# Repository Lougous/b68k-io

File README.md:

# b68k-io
IO extension board for b68k computer.

## Features
- local bus peripheral to [b68k-cpu](https://github.com/Lougous/b68k-cpu) computer
- a UART with DB9 connector (RS232, no hardware flow control)
- an I2C bus with onboard RTC chip (DS1307+) with crystal and backup battery, and 4-pins pin header extension connector
- a SPI bus with 7 chip select lines: 2x SD cards slots, 1x through an 8-pins pin header extension connector, 4x through DB15 connector for external equipements (external SPI slaves are electrically isolated from internal slaves)

Board fonctions are implemented with a PIC18F27K42 microcontroller.

The board has only two memory locations accessible through the expansion bus: one to set the actual register to access, the other to read or write data from/to the register.

| register | address | description             |
|:--------:|:-------:|:------------------------|
| DATA     | XX0000h | register data |
| ADDRESS  | XX0001h | register index |

## Register set

| register    | index   | description             |
|:-----------:|:-------:|:------------------------|
| SPI_SEL     | 0       | [5..3] : enabled SPI chip select line<br>0: external #0<br>1: external #1<br>2: external #2<br>3: external #3<br>4: SD card A<br>5: SD card B<br>6: internal pin header<br>7: none (reset) |
| SPI_CTRL    | 1       | bit 7: BUSY   r<br>bit 2: CLRBF  s<br>bit 1: TXR    rw<br>bit 0: RXR    rw |
| SPI_DATA    | 2       | SPI data in/out |
| UART_STS    | 4       | UART status<br>bit 7: TX ready<br>bit 1: RX FIFO overflow<br>bit 0: RX FIFO underflow |
| UART_DATA   | 5       | UART data in/out |
| I2C_CTRL    | 6       | bit 7: RXIF<br>bit 5: TXBE<br>bit 2: reset<br>bit 1: start<br>bit 0: RXBF |
| I2C_CNT     | 7       | |
| I2C_DATA    | 8       | |
| I2C_CMD     | 9       | bit 7..1: address<br>bit 0:    RWn |
| IRQCFG      | 14      | interrupt controller configuration<br>bit 0: enable UART RX interrupt |
| IRQSTS      | 15      | interrupt controller status<br>bit 0: UART RX interrupt pending |

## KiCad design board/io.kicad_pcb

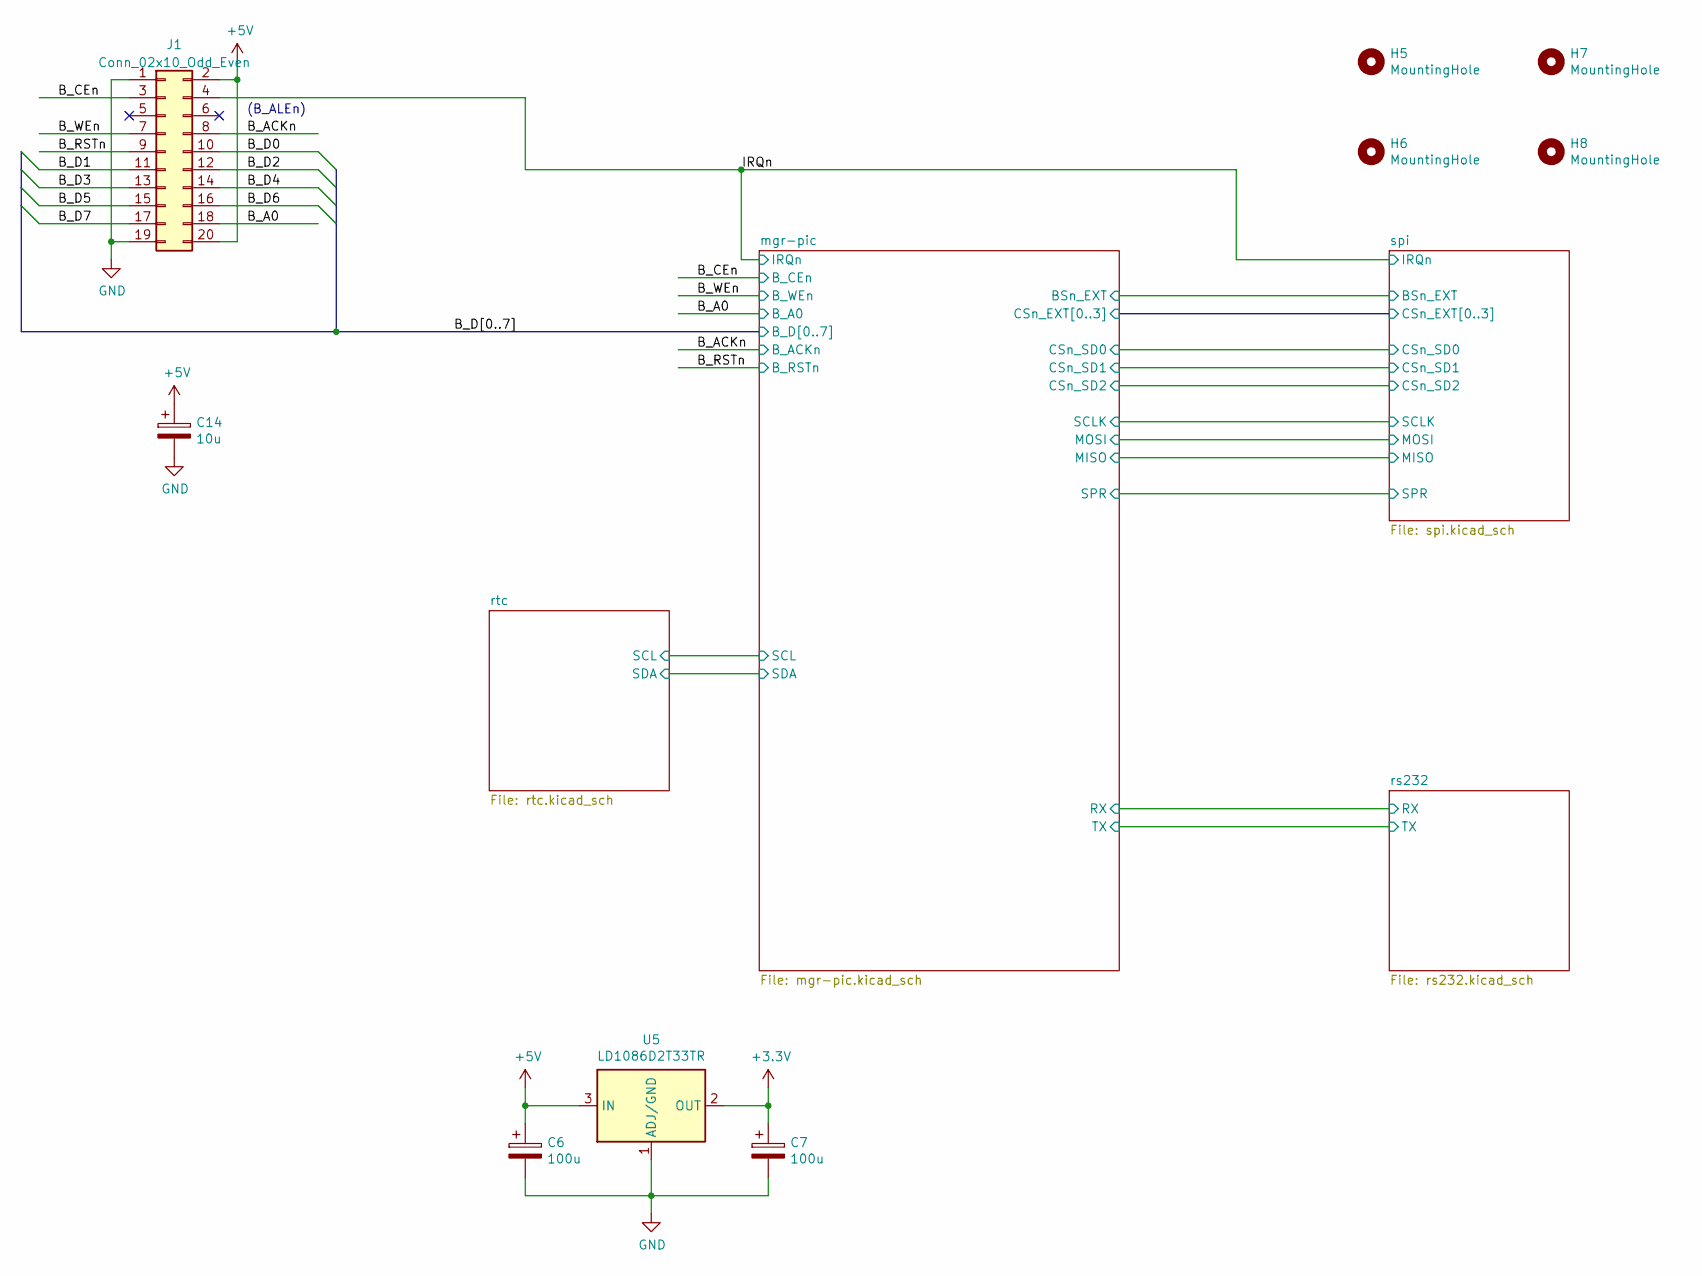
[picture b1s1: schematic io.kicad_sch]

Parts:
C6, C7: 100u; CP_Radial_D5.0mm_P2.00mm
C14: 10u; C_Disc_D4.3mm_W1.9mm_P5.00mm
H5, H6, H7, H8: MountingHole; MountingHole_2.7mm_M2.5_DIN965_Pad
J1: Conn_02x10_Odd_Even; PinSocket_2x10_P2.54mm_Vertical
U5: LD1086D2T33TR; TO-220-3_Horizontal_TabDown

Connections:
+3V3: C7.1, U5.2 (OUT); also elsewhere on the board
+5V: C6.1, C14.1, J1.2, J1.20, U5.3 (IN); also elsewhere on the board
/B_A0: J1.18; also elsewhere on the board
/B_ACKn: J1.8; also elsewhere on the board
/B_CEn: J1.3; also elsewhere on the board
/B_D0: J1.10; also elsewhere on the board
/B_D1: J1.11; also elsewhere on the board
/B_D2: J1.12; also elsewhere on the board
/B_D3: J1.13; also elsewhere on the board
/B_D4: J1.14; also elsewhere on the board
/B_D5: J1.15; also elsewhere on the board
/B_D6: J1.16; also elsewhere on the board
/B_D7: J1.17; also elsewhere on the board
/B_RSTn: J1.9; also elsewhere on the board
/B_WEn: J1.7; also elsewhere on the board
/IRQn: J1.4; also elsewhere on the board
GND: C6.2, C7.2, C14.2, J1.1, J1.19, U5.1 (ADJ/GND); also elsewhere on the board

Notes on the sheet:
(B_ALEn)

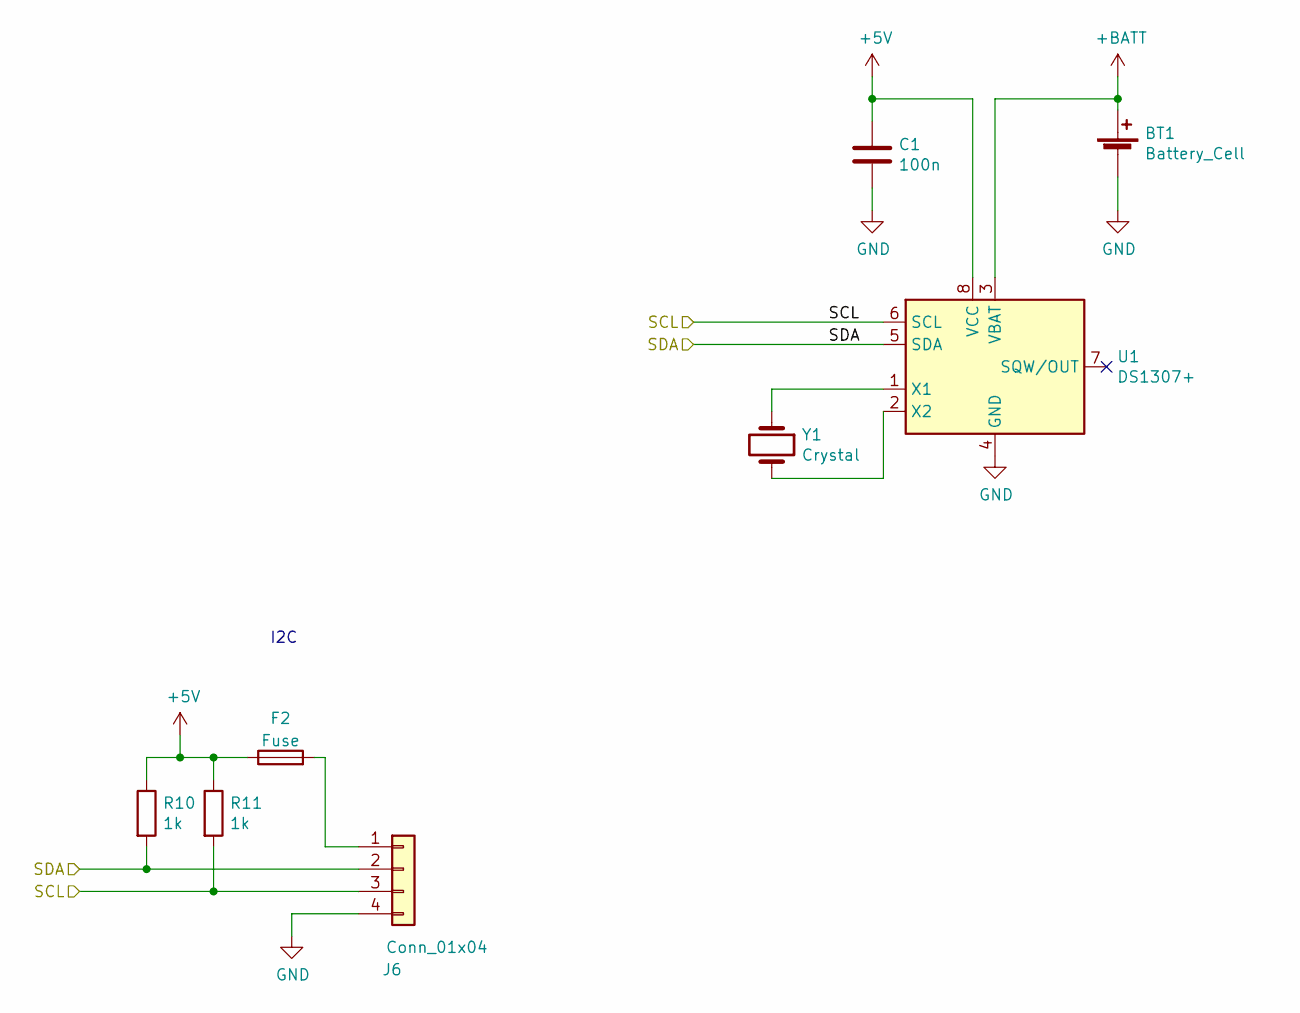
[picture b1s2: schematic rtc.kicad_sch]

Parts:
BT1: Battery_Cell; CR2032H
C1: 100n; C_Disc_D4.3mm_W1.9mm_P5.00mm
F2: Fuse; R_Axial_DIN0411_L9.9mm_D3.6mm_P5.08mm_Vertical
J6: Conn_01x04; PinHeader_1x04_P2.54mm_Horizontal
R10, R11: 1k; R_Axial_DIN0204_L3.6mm_D1.6mm_P7.62mm_Horizontal
U1: DS1307+; DIP-8_W7.62mm_Socket
Y1: Crystal; Crystal_C38-LF_D3.0mm_L8.0mm_Horizontal

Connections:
+5V: C1.1, F2.1, R10.1, R11.1, U1.8 (VCC); also elsewhere on the board
+BATT: BT1.1 (+), U1.3 (VBAT)
/mgr-pic/SCL: J6.3, R11.2, U1.6 (SCL); also elsewhere on the board
/mgr-pic/SDA: J6.2, R10.2, U1.5 (SDA); also elsewhere on the board
GND: BT1.2 (-), C1.2, J6.4, U1.4 (GND); also elsewhere on the board
unnamed: F2.2, J6.1
unnamed: U1.1 (X1), Y1.1
unnamed: U1.2 (X2), Y1.2

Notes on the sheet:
I2C

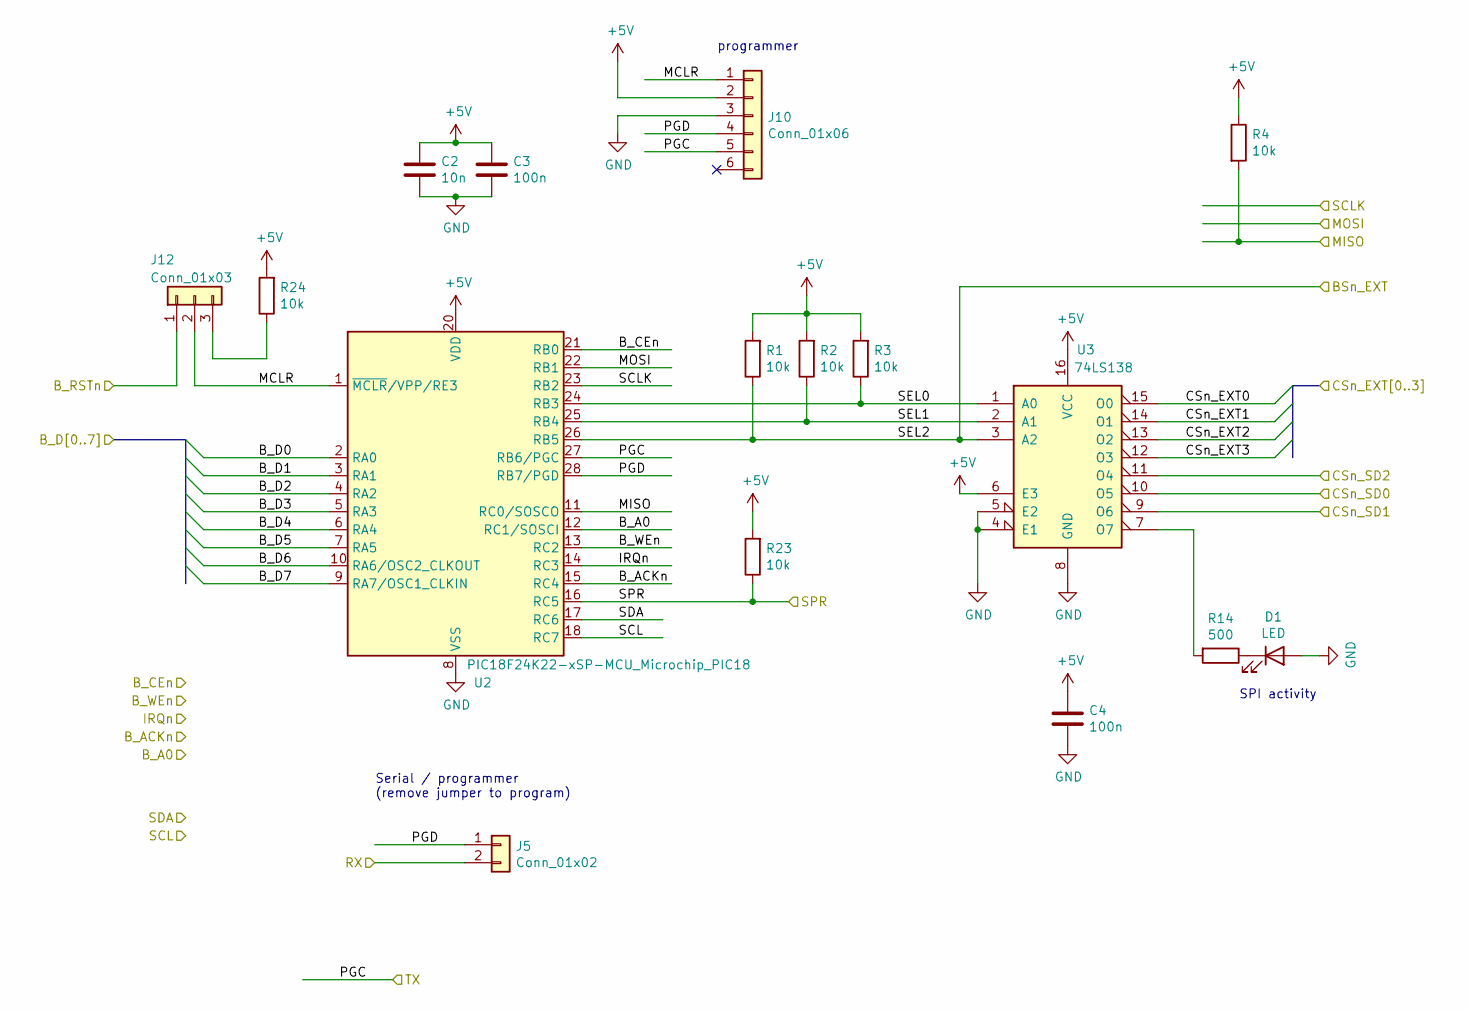
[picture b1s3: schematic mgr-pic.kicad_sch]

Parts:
C2: 10n; C_Disc_D4.3mm_W1.9mm_P5.00mm
C3, C4: 100n; C_Disc_D4.3mm_W1.9mm_P5.00mm
D1: LED; LED_D3.0mm
J5: Conn_01x02; PinHeader_1x02_P2.54mm_Vertical
J10: Conn_01x06; PinHeader_1x06_P2.54mm_Vertical
J12: Conn_01x03; PinHeader_1x03_P2.54mm_Vertical
R1, R2, R3, R4, R23, R24: 10k; R_Axial_DIN0204_L3.6mm_D1.6mm_P7.62mm_Horizontal
R14: 500; R_Axial_DIN0204_L3.6mm_D1.6mm_P7.62mm_Horizontal
U2: PIC18F24K22-xSP-MCU_Microchip_PIC18; DIP-28_W7.62mm_Socket
U3: 74LS138; DIP-16_W7.62mm_Socket

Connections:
+5V: C2.1, C3.1, C4.1, J10.2, R1.2, R2.2, R3.2, R4.1, R23.2, R24.2, U2.20 (VDD), U3.6 (E3), U3.16 (VCC); also elsewhere on the board
/B_A0: U2.12 (RC1/SOSCI); also elsewhere on the board
/B_ACKn: U2.15 (RC4); also elsewhere on the board
/B_CEn: U2.21 (RB0); also elsewhere on the board
/B_D0: U2.2 (RA0); also elsewhere on the board
/B_D1: U2.3 (RA1); also elsewhere on the board
/B_D2: U2.4 (RA2); also elsewhere on the board
/B_D3: U2.5 (RA3); also elsewhere on the board
/B_D4: U2.6 (RA4); also elsewhere on the board
/B_D5: U2.7 (RA5); also elsewhere on the board
/B_D6: U2.10 (RA6/OSC2_CLKOUT); also elsewhere on the board
/B_D7: U2.9 (RA7/OSC1_CLKIN); also elsewhere on the board
/B_RSTn: J12.1; also elsewhere on the board
/B_WEn: U2.13 (RC2); also elsewhere on the board
/IRQn: U2.14 (RC3); also elsewhere on the board
/mgr-pic/CSn_SD0: U3.10 (O5); also elsewhere on the board
/mgr-pic/CSn_SD1: U3.9 (O6); also elsewhere on the board
/mgr-pic/CSn_SD2: U3.11 (O4); also elsewhere on the board
/mgr-pic/MCLR: J10.1, J12.2, U2.1 (~MCLR/VPP/RE3)
/mgr-pic/MISO: R4.2, U2.11 (RC0/SOSCO); also elsewhere on the board
/mgr-pic/MOSI: U2.22 (RB1); also elsewhere on the board
/mgr-pic/PGC: J10.5, U2.27 (RB6/PGC); also elsewhere on the board
/mgr-pic/PGD: J5.1, J10.4, U2.28 (RB7/PGD)
/mgr-pic/RX: J5.2; also elsewhere on the board
/mgr-pic/SCL: U2.18 (RC7); also elsewhere on the board
/mgr-pic/SCLK: U2.23 (RB2); also elsewhere on the board
/mgr-pic/SDA: U2.17 (RC6); also elsewhere on the board
/mgr-pic/SEL0: R3.1, U2.24 (RB3), U3.1 (A0)
/mgr-pic/SEL1: R2.1, U2.25 (RB4), U3.2 (A1)
/mgr-pic/SEL2: R1.1, U2.26 (RB5), U3.3 (A2); also elsewhere on the board
/mgr-pic/SPR: R23.1, U2.16 (RC5); also elsewhere on the board
/spi/CSn_EXT0: U3.15 (O0); also elsewhere on the board
/spi/CSn_EXT1: U3.14 (O1); also elsewhere on the board
/spi/CSn_EXT2: U3.13 (O2); also elsewhere on the board
/spi/CSn_EXT3: U3.12 (O3); also elsewhere on the board
GND: C2.2, C3.2, C4.2, D1.2 (A), J10.3, U2.8 (VSS), U2.19 (VSS), U3.4 (E1), U3.5 (E2), U3.8 (GND); also elsewhere on the board
unnamed: D1.1 (K), R14.1
unnamed: J12.3, R24.1
unnamed: R14.2, U3.7 (O7)

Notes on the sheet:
programmer
Serial / programmer (remove jumper to program)
SPI activity

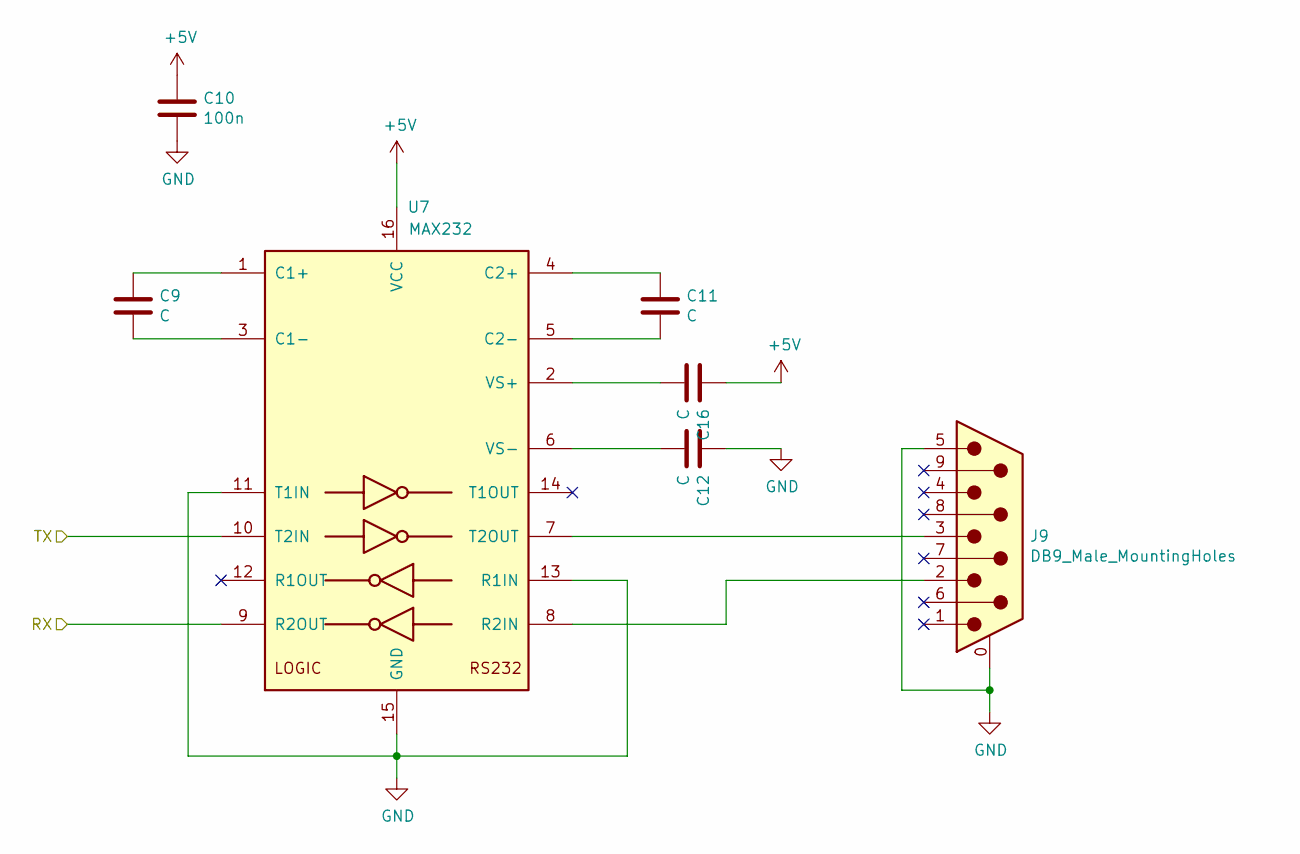
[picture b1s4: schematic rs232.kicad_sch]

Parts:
C9, C11, C12, C16: C; C_Disc_D4.3mm_W1.9mm_P5.00mm
C10: 100n; C_Disc_D4.3mm_W1.9mm_P5.00mm
J9: DB9_Male_MountingHoles; DSUB-9_Male_Horizontal_P2.77x2.84mm_EdgePinOffset9.90mm_Hou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
U7: MAX232; DIP-16_W7.62mm_Socket

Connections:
+5V: C10.1, C16.1, U7.16 (VCC); also elsewhere on the board
/mgr-pic/PGC: U7.10 (T2IN); also elsewhere on the board
/mgr-pic/RX: U7.9 (R2OUT); also elsewhere on the board
GND: C10.2, C12.1, J9.0 (PAD), J9.5, U7.11 (T1IN), U7.13 (R1IN), U7.15 (GND); also elsewhere on the board
unnamed: C9.1, U7.1 (C1+)
unnamed: C9.2, U7.3 (C1-)
unnamed: C11.1, U7.4 (C2+)
unnamed: C11.2, U7.5 (C2-)
unnamed: C12.2, U7.6 (VS-)
unnamed: C16.2, U7.2 (VS+)
unnamed: J9.2, U7.8 (R2IN)
unnamed: J9.3, U7.7 (T2OUT)

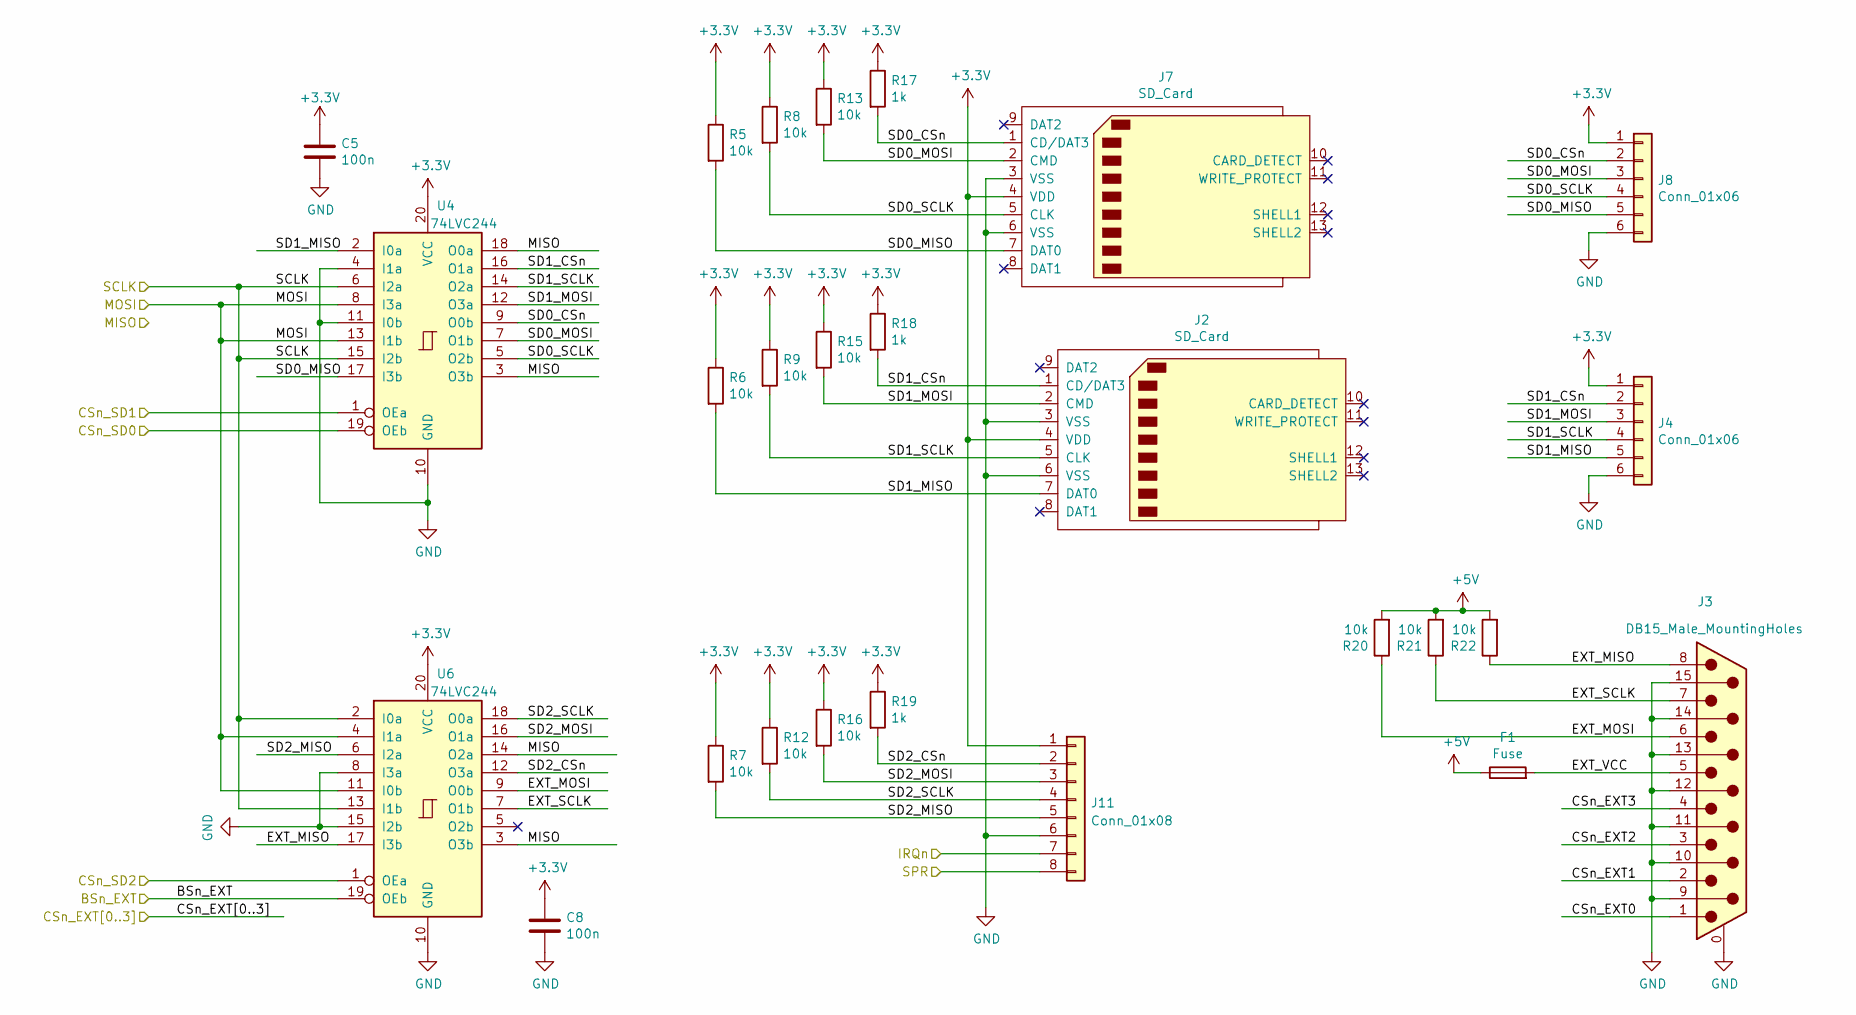
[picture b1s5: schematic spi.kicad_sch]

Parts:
C5, C8: 100n; C_Disc_D4.3mm_W1.9mm_P5.00mm
F1: Fuse; R_Axial_DIN0411_L9.9mm_D3.6mm_P5.08mm_Vertical
J2, J7: SD_Card; SD_Kyocera_145638009511859+
J3: DB15_Male_MountingHoles; DSUB-15_Male_Horizontal_P2.77x2.84mm_EdgePinOffset7.70mm_Ho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
J4, J8: Conn_01x06; PinHeader_1x06_P2.54mm_Horizontal
J11: Conn_01x08; PinHeader_1x08_P2.54mm_Vertical
R5, R6, R7, R8, R9, R12, R13, R15, R16, R20, R21, R22: 10k; R_Axial_DIN0204_L3.6mm_D1.6mm_P7.62mm_Horizontal
R17, R18, R19: 1k; R_Axial_DIN0204_L3.6mm_D1.6mm_P7.62mm_Horizontal
U4, U6: 74LVC244; DIP-20_W7.62mm_Socket

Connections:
+3V3: C5.1, C8.1, J2.4 (VDD), J4.1, J7.4 (VDD), J8.1, J11.1, R5.1, R6.1, R7.1, R8.1, R9.1, R12.1, R13.1, R15.1, R16.1, R17.1, R18.1, R19.1, U4.20 (VCC), U6.20 (VCC); also elsewhere on the board
+5V: F1.1, R20.2, R21.2, R22.2; also elsewhere on the board
/IRQn: J11.7; also elsewhere on the board
/mgr-pic/CSn_SD0: U4.19 (OEb); also elsewhere on the board
/mgr-pic/CSn_SD1: U4.1 (OEa); also elsewhere on the board
/mgr-pic/CSn_SD2: U6.1 (OEa); also elsewhere on the board
/mgr-pic/MISO: U4.3 (O3b), U4.18 (O0a), U6.3 (O3b), U6.14 (O2a); also elsewhere on the board
/mgr-pic/MOSI: U4.8 (I3a), U4.13 (I1b), U6.4 (I1a), U6.11 (I0b); also elsewhere on the board
/mgr-pic/SCLK: U4.6 (I2a), U4.15 (I2b), U6.2 (I0a), U6.13 (I1b); also elsewhere on the board
/mgr-pic/SEL2: U6.19 (OEb); also elsewhere on the board
/mgr-pic/SPR: J11.8; also elsewhere on the board
/spi/CSn_EXT0: J3.1; also elsewhere on the board
/spi/CSn_EXT1: J3.2; also elsewhere on the board
/spi/CSn_EXT2: J3.3; also elsewhere on the board
/spi/CSn_EXT3: J3.4; also elsewhere on the board
/spi/EXT_MISO: J3.8, R22.1, U6.17 (I3b)
/spi/EXT_MOSI: J3.6, R20.1, U6.9 (O0b)
/spi/EXT_SCLK: J3.7, R21.1, U6.7 (O1b)
/spi/EXT_VCC: F1.2, J3.5
/spi/SD0_CSn: J7.1 (CD/DAT3), J8.2, R17.2, U4.9 (O0b)
/spi/SD0_MISO: J7.7 (DAT0), J8.5, R5.2, U4.17 (I3b)
/spi/SD0_MOSI: J7.2 (CMD), J8.3, R13.2, U4.7 (O1b)
/spi/SD0_SCLK: J7.5 (CLK), J8.4, R8.2, U4.5 (O2b)
/spi/SD1_CSn: J2.1 (CD/DAT3), J4.2, R18.2, U4.16 (O1a)
/spi/SD1_MISO: J2.7 (DAT0), J4.5, R6.2, U4.2 (I0a)
/spi/SD1_MOSI: J2.2 (CMD), J4.3, R15.2, U4.12 (O3a)
/spi/SD1_SCLK: J2.5 (CLK), J4.4, R9.2, U4.14 (O2a)
/spi/SD2_CSn: J11.2, R19.2, U6.12 (O3a)
/spi/SD2_MISO: J11.5, R7.2, U6.6 (I2a)
/spi/SD2_MOSI: J11.3, R16.2, U6.16 (O1a)
/spi/SD2_SCLK: J11.4, R12.2, U6.18 (O0a)
GND: C5.2, C8.2, J2.3 (VSS), J2.6 (VSS), J3.0 (PAD), J3.9, J3.10, J3.11 (P111), J3.12, J3.13, J3.14, J3.15, J4.6, J7.3 (VSS), J7.6 (VSS), J8.6, J11.6, U4.4 (I1a), U4.10 (GND), U4.11 (I0b), U6.8 (I3a), U6.10 (GND), U6.15 (I2b); also elsewhere on the board

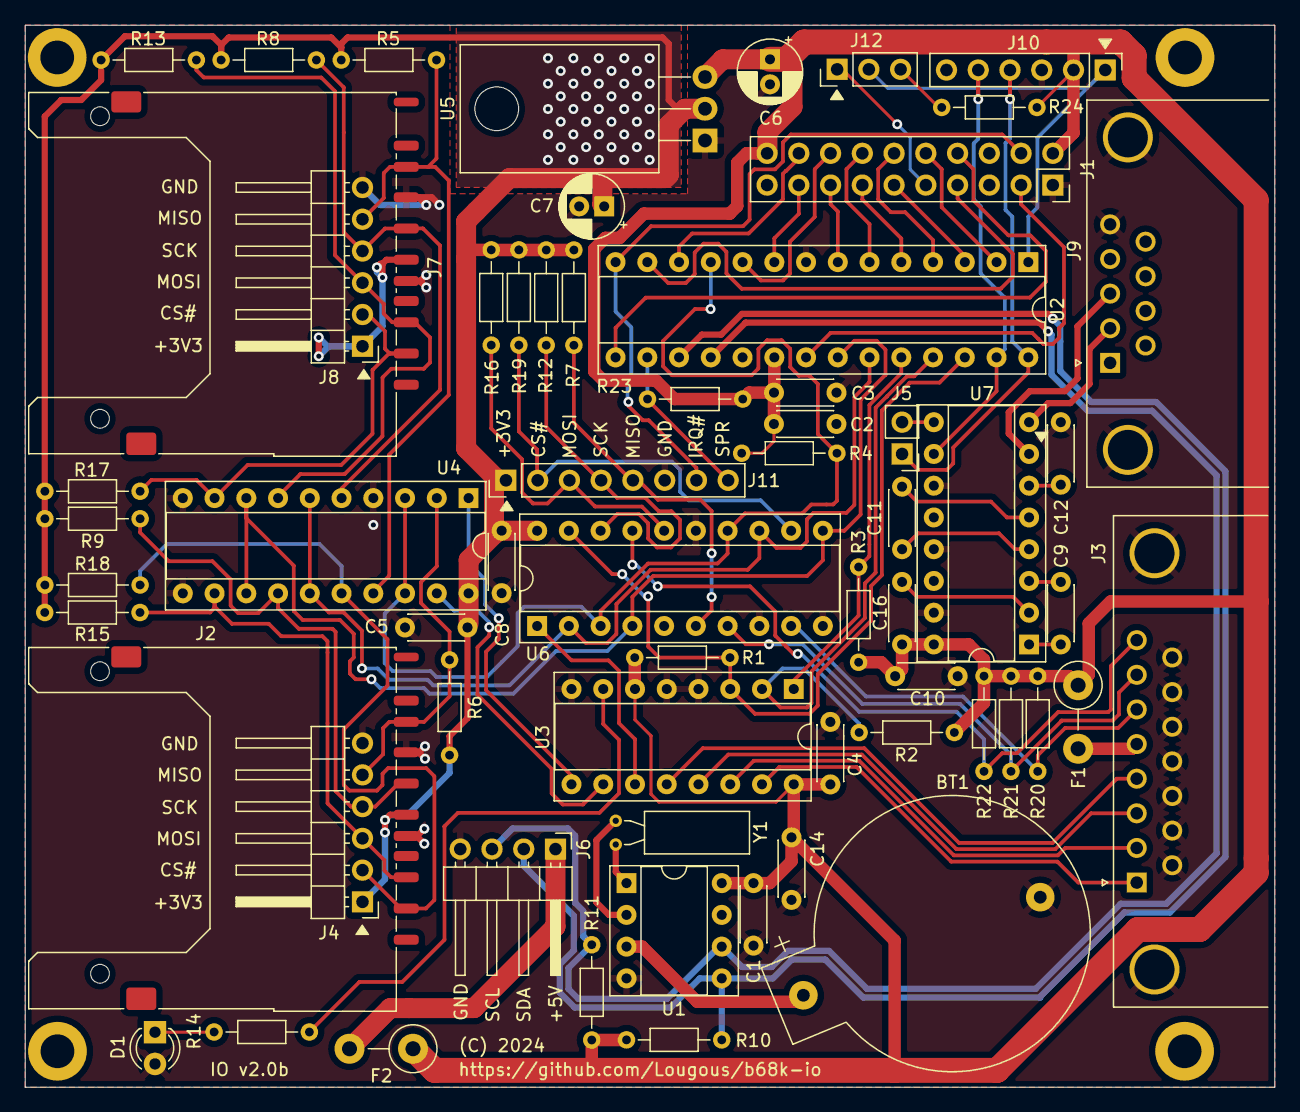
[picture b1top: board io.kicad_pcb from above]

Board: 2 copper layers, 100.0 x 85.0 mm, 66 parts (0 on the bottom side), 68 nets.

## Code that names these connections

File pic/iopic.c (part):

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#pragma config FCMEN = ON       // Fail-Safe Clock Monitor Enable bit (Fail-Safe Clock Monitor enabled)

// CONFIG2L
#pragma config MCLRE = EXTMCLR  // MCLR Enable bit (If LVP = 0, MCLR pin is MCLR; If LVP = 1, RE3 pin function is MCLR )
#pragma config PWRTS = PWRT_OFF // Power-up timer selection bits (PWRT is disabled)
#pragma config MVECEN = ON      // Multi-vector enable bit (Multi-vector enabled, Vector table used for interrupts)
#pragma config IVT1WAY = ON     // IVTLOCK bit One-way set enable bit (IVTLOCK bit can be cleared and set only once)
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#pragma config WRTC = OFF       // Boot Block Write Protection bit (Boot Block (000000-0007FFh) not write-protected)
#pragma config WRTD = OFF       // Data EEPROM Write Protection bit (Data EEPROM not write-protected)
#pragma config WRTSAF = OFF     // SAF Write protection bit (SAF not Write Protected)
#pragma config LVP = ON         // Low Voltage Programming Enable bit (Low voltage programming enabled. MCLR/VPP pin function is MCLR. MCLRE configuration bit is ignored)

// CONFIG5L
#pragma config CP = OFF         // PFM and Data EEPROM Code Protection bit (PFM and Data EEPROM code protection disabled)
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    U1TXB = data;                     // send one character
}

#define CEn              (PORTBbits.RB0)

//#define RSTn             (PORTBbits.RB3)
//#define ASSERT_RSTn      TRISBbits.TRISB3 = 0;   // output - RST# asserted
//#define DEASSERT_RSTn    TRISBbits.TRISB3 = 1;   // input - RST# deasserted
//
#define ACKn             (PORTCbits.RC4)
#define ASSERT_ACKn      TRISCbits.TRISC4 = 0;   // output - ACK# asserted
#define DEASSERT_ACKn    TRISCbits.TRISC4 = 1;   // input - ACK# deasserted

#define IRQn             (PORTCbits.RC3)
#define ASSERT_IRQn      TRISCbits.TRISC3 = 0;   // output - ACK# asserted
#define DEASSERT_IRQn    TRISCbits.TRISC3 = 1;   // input - ACK# deasserted

#define WEn              (PORTCbits.RC2)

#define A0               (PORTCbits.RC1)

#define SPR              (PORTCbits.RC5)

// RB3, RB4, RB5
#define SET_SEL(val)     LATB = ((LATB & ~0x38) | (val & 0x38))
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    // chip select
    SET_SEL(CS_NONE);  // no chip
    // note: while input, pull-ups oper
    TRISBbits.TRISB3 = 0;   // output - SEL0
    TRISBbits.TRISB4 = 0;   // output - SEL1
    TRISBbits.TRISB5 = 0;   // output - SEL2

    ////////////////////////////////////////////////////////////////////////////
    // config & status
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    U1BRGH=0;

    //set uart 1 pins
    // TX: PGC / RB6 (pin 27)
    TRISBbits.TRISB6 = 0;   // output
    RB6PPS=0b00010011;
  
    // RX: PGD / RB7 (pin 28)
    TRISBbits.TRISB7 = 1;   // input
    U1RXPPS=0b00001111;
    
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
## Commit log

2024-06-04 import board files
2024-06-07 more KiCAD filters
2024-06-07 add title
2024-06-07 export schematics to PDF
2024-06-11 add documentation
2024-06-11 microcontroller software

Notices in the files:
board/io.kicad_pcb:
(C) 2024
